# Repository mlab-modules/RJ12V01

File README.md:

# RJ12V01A - RJ12 connector module

Module with RJ12 connector, which is used primarily for connecting sensors.

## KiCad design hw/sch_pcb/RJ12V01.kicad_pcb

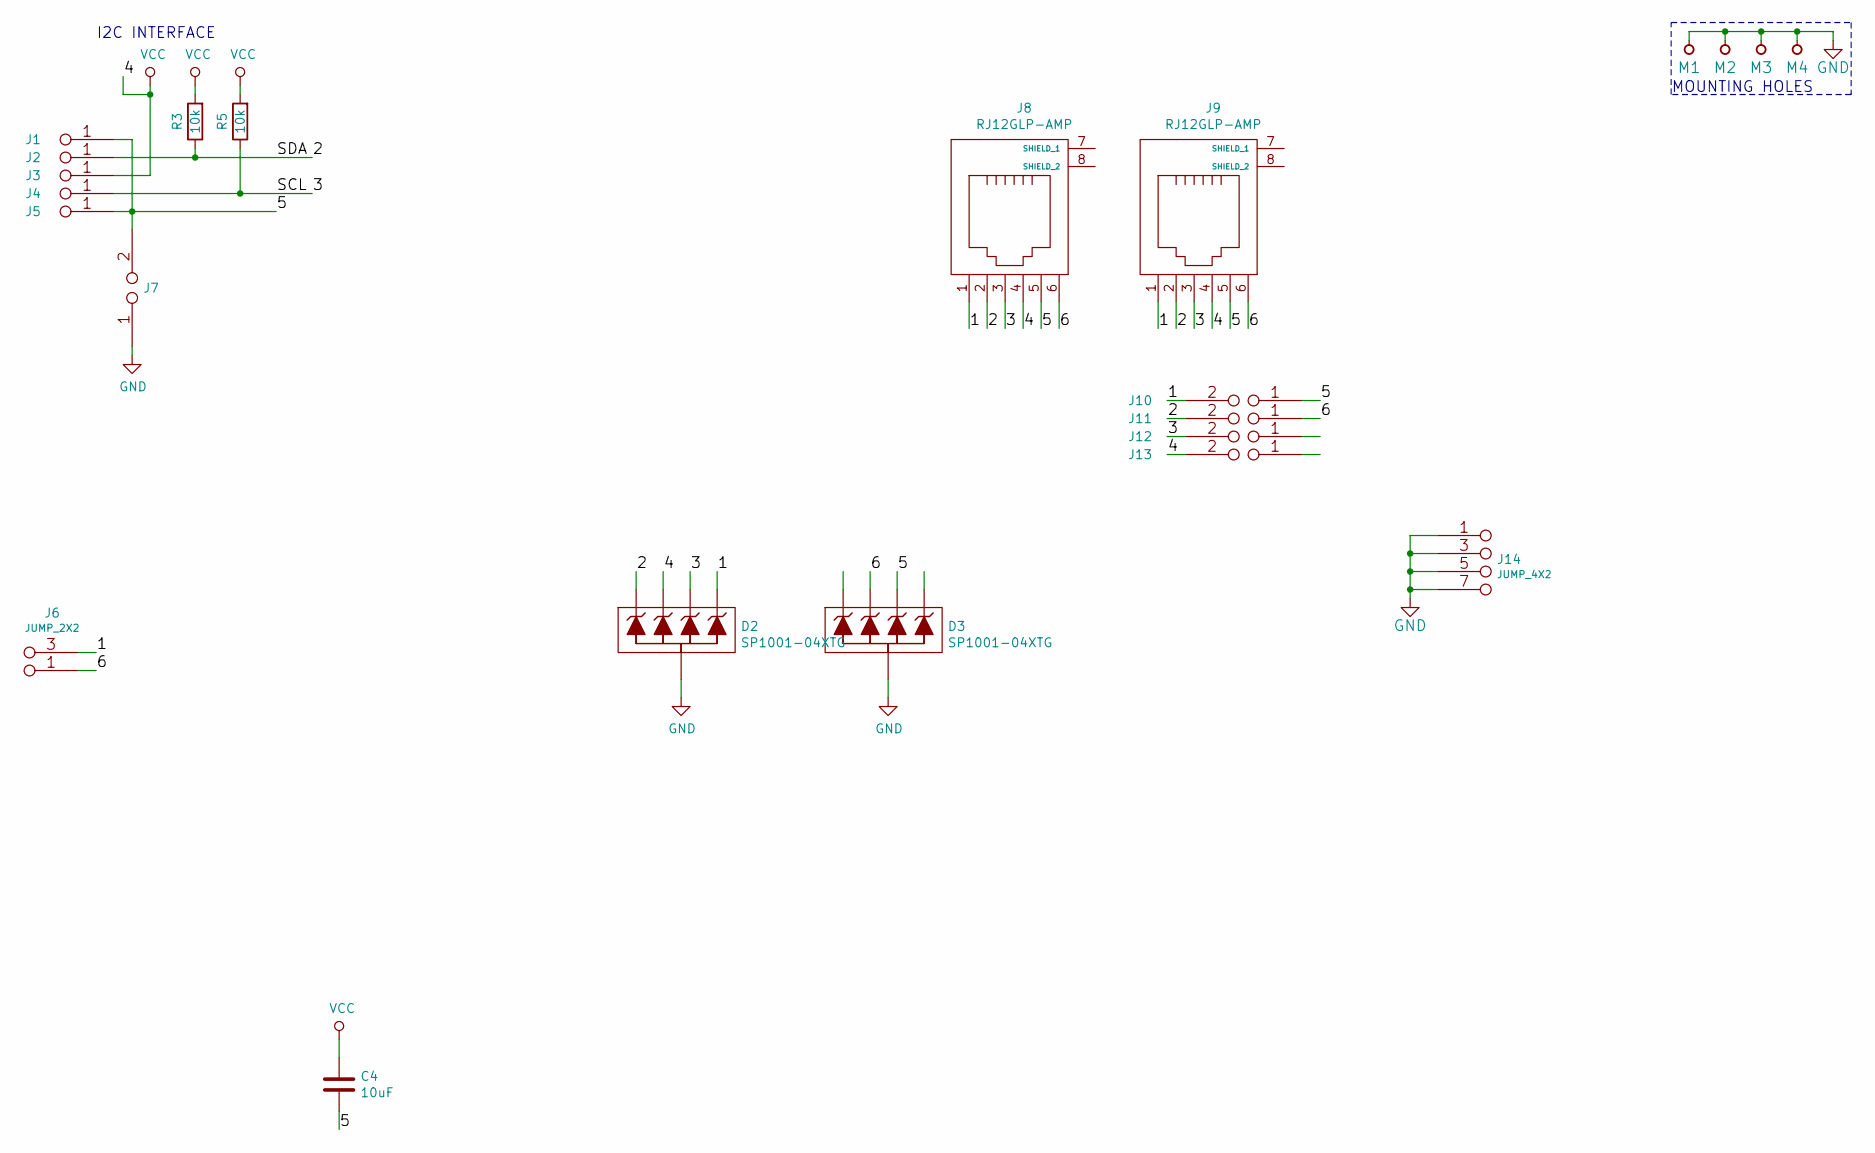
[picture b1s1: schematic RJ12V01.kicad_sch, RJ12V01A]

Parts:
C4: 10uF; SMD-0805
D2, D3: SP1001-04XTG; SOT-553
J1, J2, J3, J4, J5: JUMP_2x1; Straight_2x01
J6: JUMP_2X2; Straight_2x02
J7, J10, J11, J12, J13: JUMP2_2x1; Straight_2x01
J8, J9: RJ12GLP-AMP; RJ12GLP-AMP(RJ12)
J14: JUMP_4X2; Straight_2x04
M1, M2, M3, M4: HOLE; MountingHole_3mm
R3, R5: 10k; SMD-0805

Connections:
/1: D2.5, J6.3 (4), J6.4, J8.1, J9.1, J10.2
/2: D2.1, J2.1, J2.2, J8.2, J9.2, J11.2, R3.1
/3: D2.4, J4.1, J4.2, J8.3, J9.3, J12.2, R5.1
/5: C4.2, D3.4, J1.1, J1.2, J5.1, J5.2, J7.2, J8.5, J9.5, J10.1
/6: D3.3, J6.1, J6.2 (1), J8.6, J9.6, J11.1
GND: D2.2, D3.2, J7.1, J14.1 (2), J14.2, J14.3 (4), J14.4, J14.5, J14.6 (5), J14.7 (8), J14.8, M1.1, M2.1, M3.1, M4.1
VCC: C4.1, D2.3, J3.1, J3.2, J8.4, J9.4, J13.2, R3.2, R5.2

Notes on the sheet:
I2C INTERFACE
MOUNTING HOLES

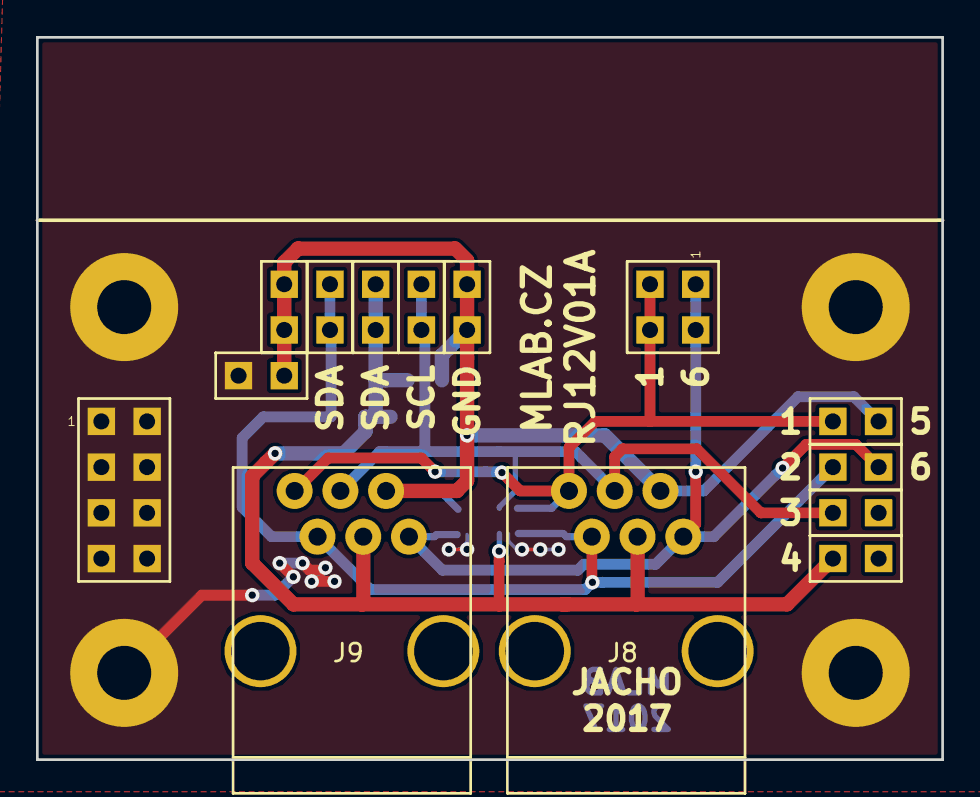
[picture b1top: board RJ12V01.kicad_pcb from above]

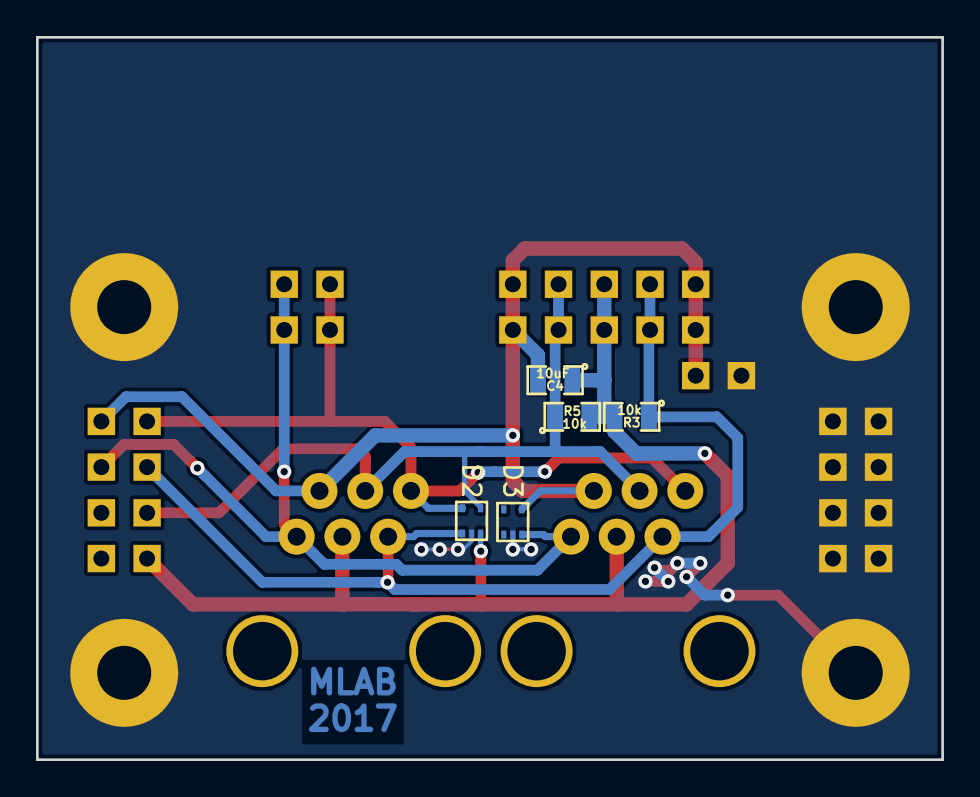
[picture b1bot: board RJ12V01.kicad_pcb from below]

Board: 2 copper layers, 50.3 x 40.1 mm, 23 parts (5 on the bottom side), 7 nets.

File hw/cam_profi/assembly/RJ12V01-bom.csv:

Component,Description,Part,References,Value,Footprint,Quantity Per PCB,Datasheet
1,,C,C4,10uF,SMD-0805,1,
2,,D_4xZENER,D2D3,SP1001-04XTG,SOT-553,2,
3,,JUMP2_2x1,J7J10J11J12J13,JUMP2_2x1,Straight_2x01,5,
4,,JUMP_2X2,J6,JUMP_2X2,Straight_2x02,1,
5,,JUMP_2x1,J1J2J3J4J5,JUMP_2x1,Straight_2x01,5,
6,,JUMP_4X2,J14,JUMP_4X2,Straight_2x04,1,
7,,RJ12,J8J9,RJ12GLP-AMP,RJ12GLP-AMP(RJ12),2,
8,,R,R3R5,10k,SMD-0805,2,

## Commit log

2023-04-01 Adding force option to enable splitting in not fresh copy of Modules repository.
2023-09-17 automated commit; add github actions
2023-09-17 Update workflow files
2023-09-17 Update metadata files
2024-07-06 Update to KiCadv7
2024-07-06 Update actions products
2024-07-06 Update documentation.
